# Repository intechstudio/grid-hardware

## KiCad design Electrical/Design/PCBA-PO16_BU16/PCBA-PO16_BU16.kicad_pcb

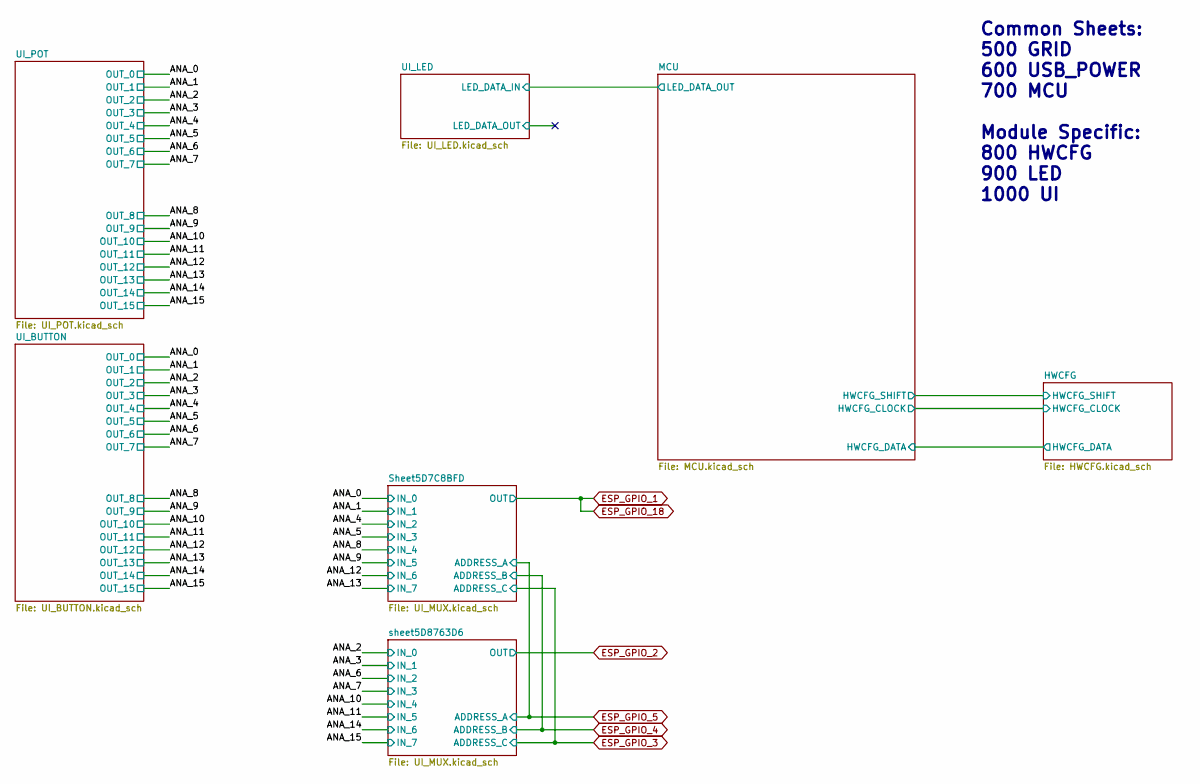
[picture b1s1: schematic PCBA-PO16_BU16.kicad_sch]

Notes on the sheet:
Common Sheets: 500 GRID 600 USB_POWER 700 MCU Module Specific: 800 HWCFG 900 LED 1000 UI

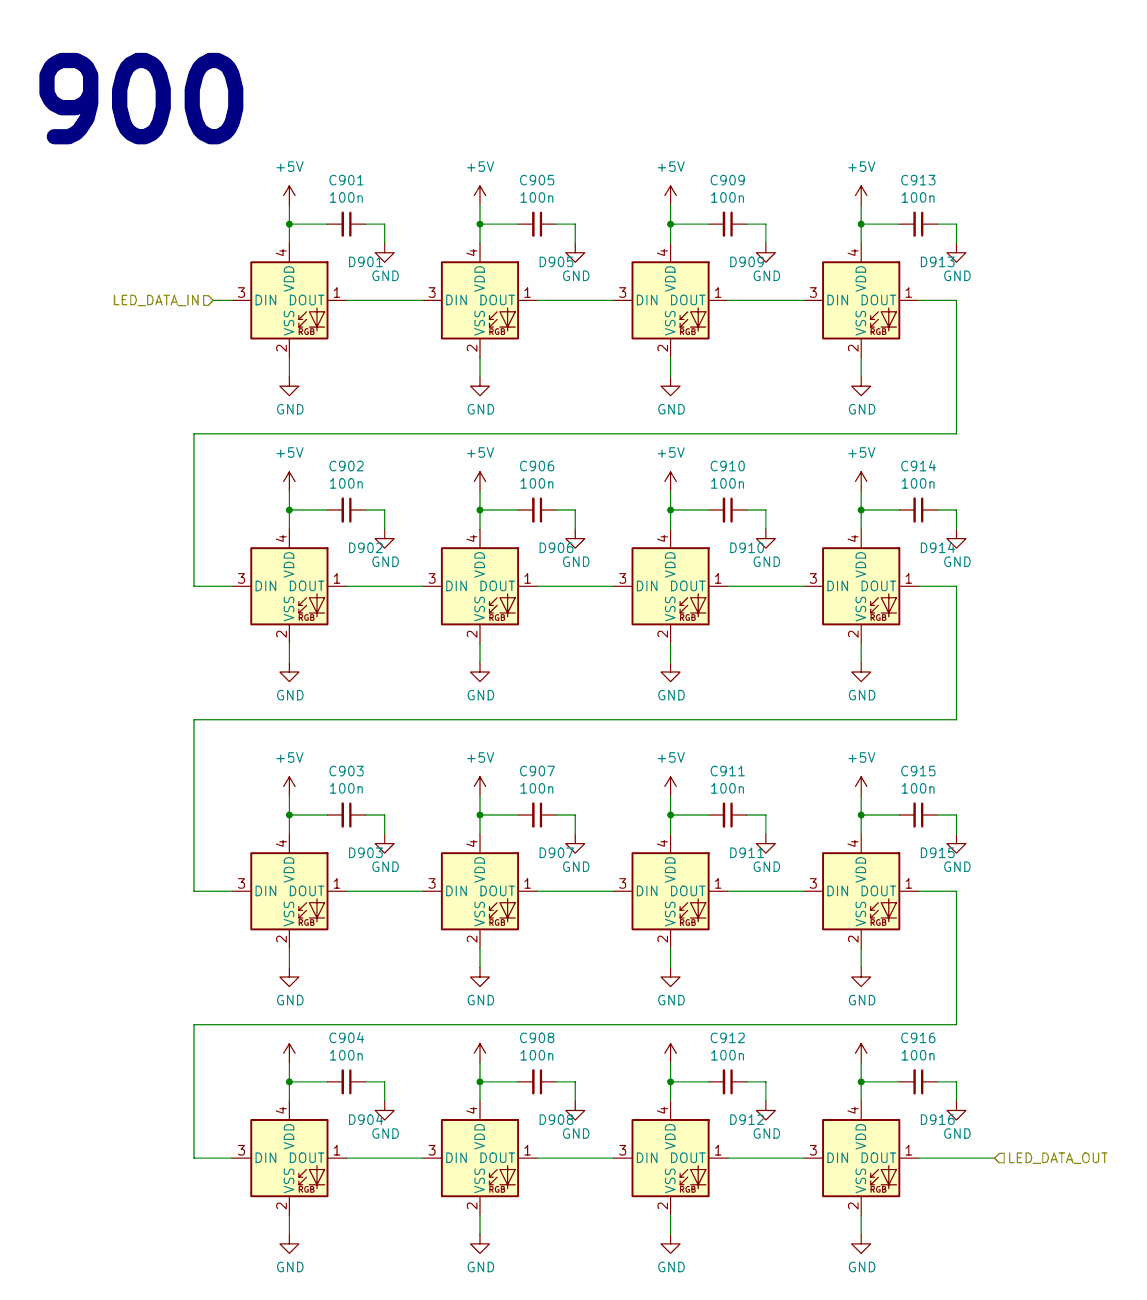
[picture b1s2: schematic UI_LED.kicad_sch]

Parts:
C901, C902, C903, C904, C905, C906, C907, C908, C909, C910, C911, C912, C913, C914, C915, C916: 100n; CAP_0402
D901, D902, D903, D904, D905, D906, D907, D908, D909, D910, D911, D912, D913, D914, D915, D916: WS2812C-2020; UI_WS2812C-2020

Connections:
+5V: C901.2, C902.2, C903.2, C904.2, C905.2, C906.2, C907.2, C908.2, C909.2, C910.2, C911.2, C912.2, C913.2, C914.2, C915.2, C916.2, D901.4 (VDD), D902.4 (VDD), D903.4 (VDD), D904.4 (VDD), D905.4 (VDD), D906.4 (VDD), D907.4 (VDD), D908.4 (VDD), D909.4 (VDD), D910.4 (VDD), D911.4 (VDD), D912.4 (VDD), D913.4 (VDD), D914.4 (VDD), D915.4 (VDD), D916.4 (VDD); also elsewhere on the board
/MCU/LED_DATA_OUT: D901.3 (DIN); also elsewhere on the board
/UI_LED/LED_DATA_OUT: D916.1 (DOUT)
unnamed: D901.1 (DOUT), D905.3 (DIN)
unnamed: D902.3 (DIN), D913.1 (DOUT)
unnamed: D902.1 (DOUT), D906.3 (DIN)
unnamed: D903.3 (DIN), D914.1 (DOUT)
unnamed: D903.1 (DOUT), D907.3 (DIN)
unnamed: D904.3 (DIN), D915.1 (DOUT)
unnamed: D904.1 (DOUT), D908.3 (DIN)
unnamed: D905.1 (DOUT), D909.3 (DIN)
unnamed: D906.1 (DOUT), D910.3 (DIN)
unnamed: D907.1 (DOUT), D911.3 (DIN)
unnamed: D908.1 (DOUT), D912.3 (DIN)
unnamed: D909.1 (DOUT), D913.3 (DIN)
unnamed: D910.1 (DOUT), D914.3 (DIN)
unnamed: D911.1 (DOUT), D915.3 (DIN)
unnamed: D912.1 (DOUT), D916.3 (DIN)

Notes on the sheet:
900

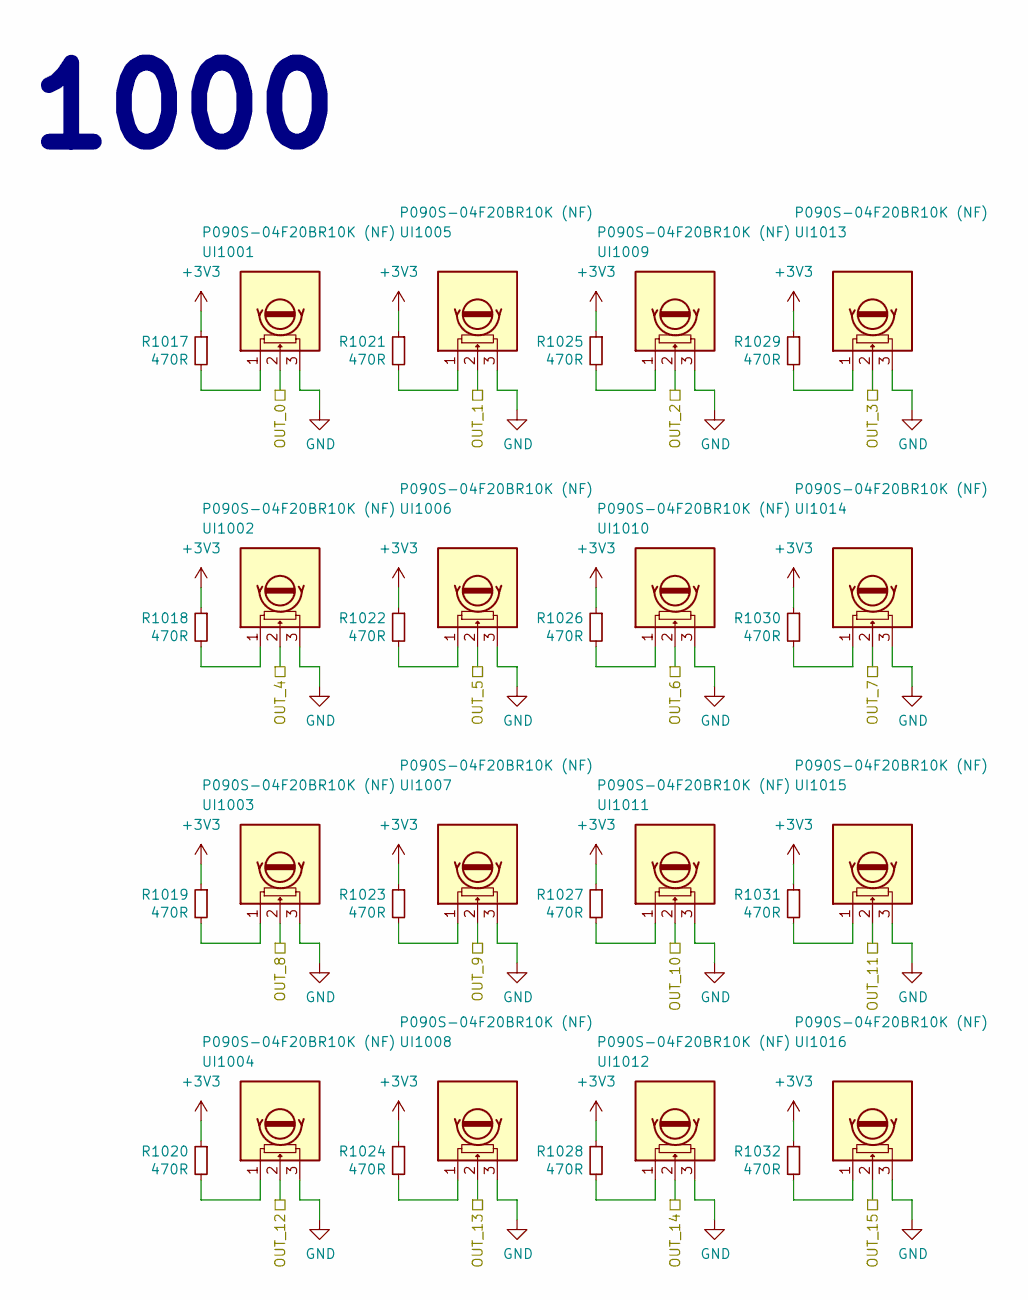
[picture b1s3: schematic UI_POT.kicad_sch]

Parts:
R1017, R1018, R1019, R1020, R1021, R1022, R1023, R1024, R1025, R1026, R1027, R1028, R1029, R1030, R1031, R1032: 470R; RES_0402
UI1001, UI1002, UI1003, UI1004, UI1005, UI1006, UI1007, UI1008, UI1009, UI1010, UI1011, UI1012, UI1013, UI1014, UI1015, UI1016: P090S-04F20BR10K (NF); UI_POT_TT

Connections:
/ANA_0: UI1001.2; also elsewhere on the board
/ANA_1: UI1005.2; also elsewhere on the board
/ANA_2: UI1009.2; also elsewhere on the board
/ANA_3: UI1013.2; also elsewhere on the board
/ANA_4: UI1002.2; also elsewhere on the board
/ANA_5: UI1006.2; also elsewhere on the board
/ANA_6: UI1010.2; also elsewhere on the board
/ANA_7: UI1014.2; also elsewhere on the board
/ANA_8: UI1003.2; also elsewhere on the board
/ANA_9: UI1007.2; also elsewhere on the board
/ANA_10: UI1011.2; also elsewhere on the board
/ANA_11: UI1015.2; also elsewhere on the board
/ANA_12: UI1004.2; also elsewhere on the board
/ANA_13: UI1008.2; also elsewhere on the board
/ANA_14: UI1012.2; also elsewhere on the board
/ANA_15: UI1016.2; also elsewhere on the board
unnamed: R1017.2, UI1001.1
unnamed: R1018.2, UI1002.1
unnamed: R1019.2, UI1003.1
unnamed: R1020.2, UI1004.1
unnamed: R1021.2, UI1005.1
unnamed: R1022.2, UI1006.1
unnamed: R1023.2, UI1007.1
unnamed: R1024.2, UI1008.1
unnamed: R1025.2, UI1009.1
unnamed: R1026.2, UI1010.1
unnamed: R1027.2, UI1011.1
unnamed: R1028.2, UI1012.1
unnamed: R1029.2, UI1013.1
unnamed: R1030.2, UI1014.1
unnamed: R1031.2, UI1015.1
unnamed: R1032.2, UI1016.1

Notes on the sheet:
1000

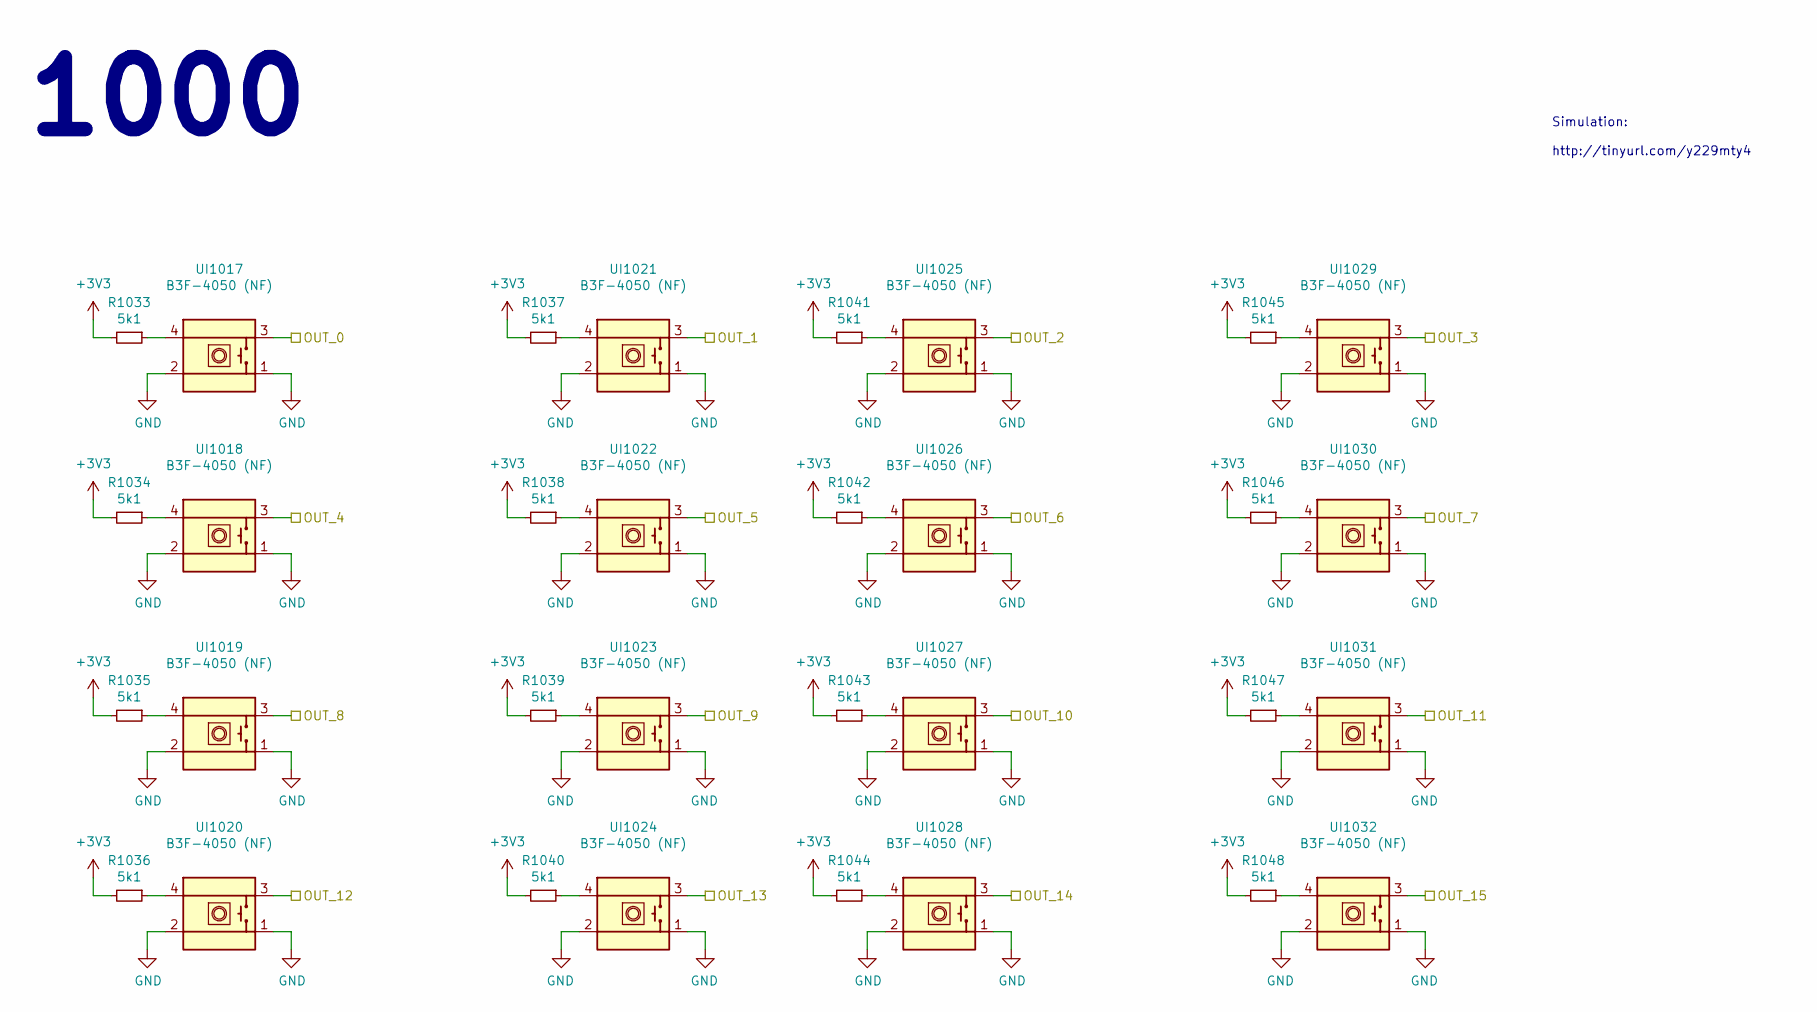
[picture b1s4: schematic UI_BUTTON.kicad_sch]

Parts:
R1033, R1034, R1035, R1036, R1037, R1038, R1039, R1040, R1041, R1042, R1043, R1044, R1045, R1046, R1047, R1048: 5k1; RES_0402
UI1017, UI1018, UI1019, UI1020, UI1021, UI1022, UI1023, UI1024, UI1025, UI1026, UI1027, UI1028, UI1029, UI1030, UI1031, UI1032: B3F-4050 (NF); UI_BUTTON_OMRON

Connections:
/ANA_0: UI1017.3; also elsewhere on the board
/ANA_1: UI1021.3; also elsewhere on the board
/ANA_2: UI1025.3; also elsewhere on the board
/ANA_3: UI1029.3; also elsewhere on the board
/ANA_4: UI1018.3; also elsewhere on the board
/ANA_5: UI1022.3; also elsewhere on the board
/ANA_6: UI1026.3; also elsewhere on the board
/ANA_7: UI1030.3; also elsewhere on the board
/ANA_8: UI1019.3; also elsewhere on the board
/ANA_9: UI1023.3; also elsewhere on the board
/ANA_10: UI1027.3; also elsewhere on the board
/ANA_11: UI1031.3; also elsewhere on the board
/ANA_12: UI1020.3; also elsewhere on the board
/ANA_13: UI1024.3; also elsewhere on the board
/ANA_14: UI1028.3; also elsewhere on the board
/ANA_15: UI1032.3; also elsewhere on the board
unnamed: R1033.1, UI1017.4
unnamed: R1034.1, UI1018.4
unnamed: R1035.1, UI1019.4
unnamed: R1036.1, UI1020.4
unnamed: R1037.1, UI1021.4
unnamed: R1038.1, UI1022.4
unnamed: R1039.1, UI1023.4
unnamed: R1040.1, UI1024.4
unnamed: R1041.1, UI1025.4
unnamed: R1042.1, UI1026.4
unnamed: R1043.1, UI1027.4
unnamed: R1044.1, UI1028.4
unnamed: R1045.1, UI1029.4
unnamed: R1046.1, UI1030.4
unnamed: R1047.1, UI1031.4
unnamed: R1048.1, UI1032.4

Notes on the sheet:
1000
Simulation: http://tinyurl.com/y229mty4

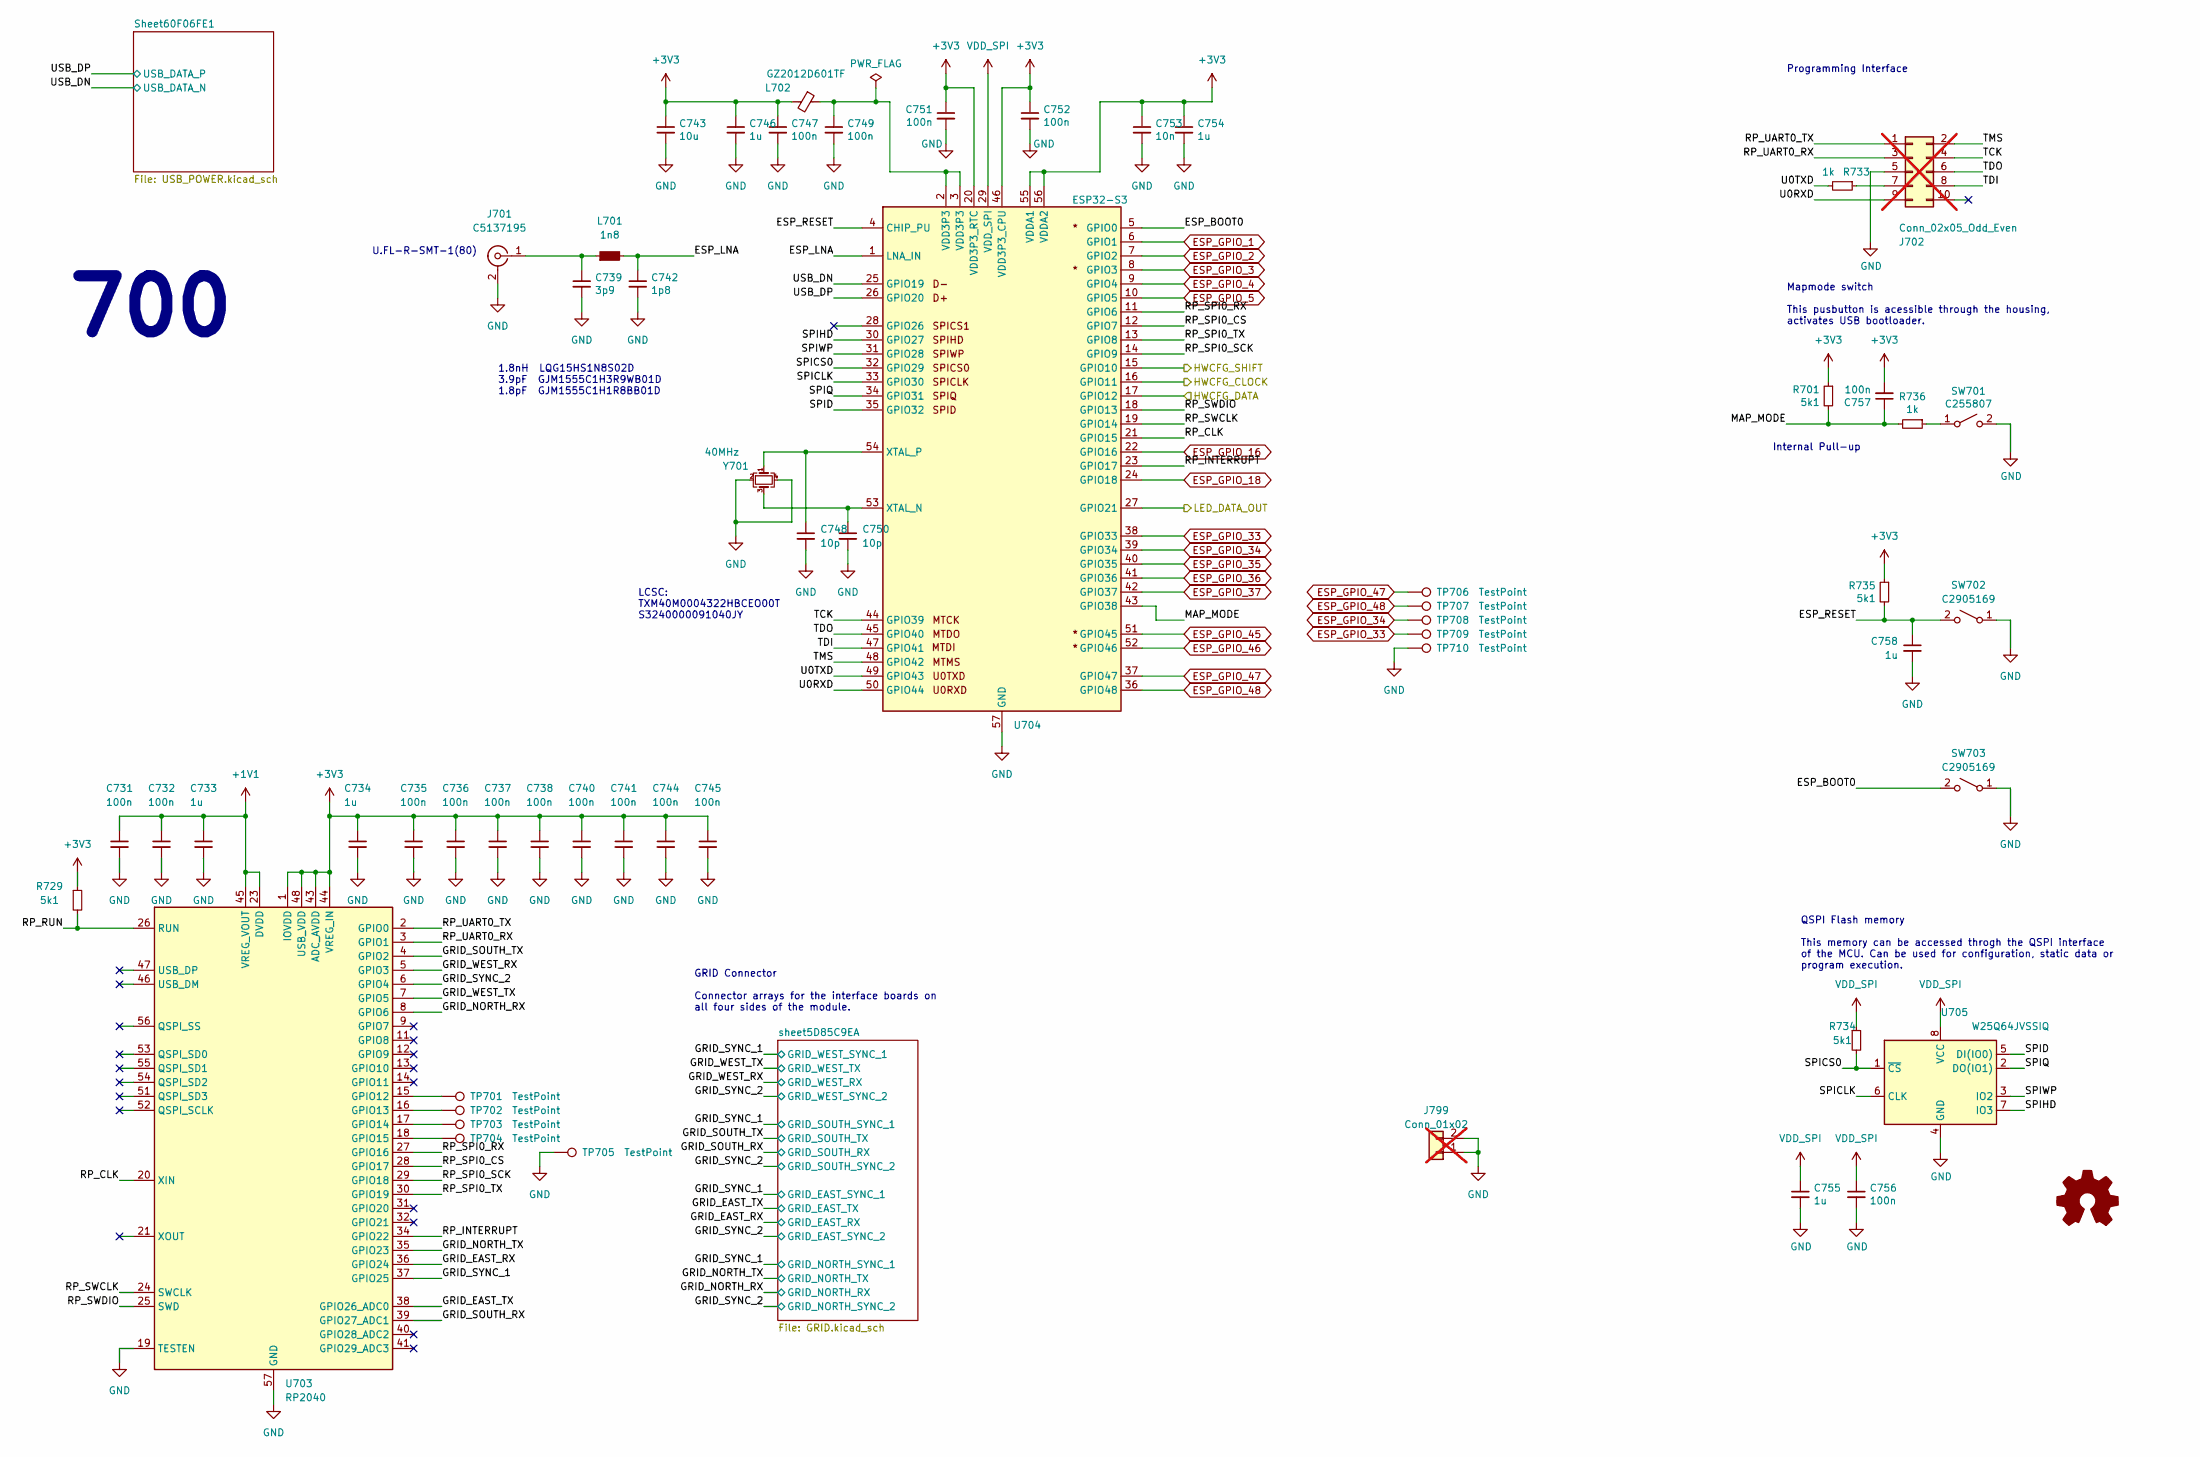
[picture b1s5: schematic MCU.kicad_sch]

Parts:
C731, C732, C735, C736, C737, C738, C740, C741, C744, C745, C747, C749, C751, C752, C756, C757: 100n; CAP_0402
C733, C734, C746, C754, C755, C758: 1u; CAP_0402
C739: 3p9; CAP_0402
C742: 1p8; CAP_0402
C743: 10u; CAP_0402
C748, C750: 10p; CAP_0402
C753: 10n; CAP_0402
J701: C5137195; U.FL_Molex_MCRF_73412-0110_Vertical
J702: Conn_02x05_Odd_Even; PinHeader_2x05_P1.27mm_Vertical; not fitted
J799: Conn_01x02; OscilloscopeGround; not fitted
L701: 1n8; IND_0402
L702: GZ2012D601TF; FERRIT_0805
LOGO701: OSHWA
R701, R729, R734, R735: 5k1; RES_0402
R733, R736: 1k; RES_0402
SW701: C255807; SW_HYP_MAPMODE
SW702, SW703: C2905169; SW_SPST_CK_RS282G05A3
TP701, TP702, TP703, TP704, TP706, TP707, TP708, TP709: TestPoint; TestPoint_Pad_D1.0mm
TP705, TP710: TestPoint; TestPoint_Pad_1.0x1.0mm
U703: RP2040; RP2040_QFN-56-1EP_7x7mm_P0.4mm_EP3.2x3.2mm
U704: ESP32-S3; QFN-56-1EP_7x7mm_P0.4mm_EP3.2x3.2mm
U705: W25Q64JVSSIQ; SOIC-8W_FLASH
Y701: 40MHz; Crystal_SMD_Abracon_ABM8G-4Pin_3.2x2.5mm

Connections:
+1V1: C731.1, C732.1, C733.1, U703.23 (DVDD), U703.45 (VREG_VOUT), U703.50 (DVDD)
/HWCFG/HWCFG_CLOCK: U704.16 (GPIO11); also elsewhere on the board
/HWCFG/HWCFG_DATA: U704.17 (GPIO12); also elsewhere on the board
/HWCFG/HWCFG_SHIFT: U704.15 (GPIO10); also elsewhere on the board
/MCU/ESP_BOOT0: SW703.2 (B), U704.5 (GPIO0)
/MCU/ESP_LNA: C742.1, L701.2, U704.1 (LNA_IN)
/MCU/ESP_RESET: C758.1, R735.2, SW702.2 (B), U704.4 (CHIP_PU)
/MCU/GRID_EAST_RX: U703.36 (GPIO24); also elsewhere on the board
/MCU/GRID_EAST_TX: U703.38 (GPIO26_ADC0); also elsewhere on the board
/MCU/GRID_NORTH_RX: U703.8 (GPIO6); also elsewhere on the board
/MCU/GRID_NORTH_TX: U703.35 (GPIO23); also elsewhere on the board
/MCU/GRID_SOUTH_RX: U703.39 (GPIO27_ADC1); also elsewhere on the board
/MCU/GRID_SOUTH_TX: U703.4 (GPIO2); also elsewhere on the board
/MCU/GRID_SYNC_1: U703.37 (GPIO25); also elsewhere on the board
/MCU/GRID_SYNC_2: U703.6 (GPIO4); also elsewhere on the board
/MCU/GRID_WEST_RX: U703.5 (GPIO3); also elsewhere on the board
/MCU/GRID_WEST_TX: U703.7 (GPIO5); also elsewhere on the board
/MCU/LED_DATA_OUT: U704.27 (GPIO21); also elsewhere on the board
/MCU/MAP_MODE: C757.1, R701.2, R736.2, U704.43 (GPIO38)
/MCU/RP_CLK: U703.20 (XIN), U704.21 (GPIO15)
/MCU/RP_INTERRUPT: U703.34 (GPIO22), U704.23 (GPIO17)
/MCU/RP_RUN: R729.2, U703.26 (RUN)
/MCU/RP_SPI0_CS: U703.28 (GPIO17), U704.12 (GPIO7)
/MCU/RP_SPI0_RX: U703.27 (GPIO16), U704.11 (GPIO6)
/MCU/RP_SPI0_SCK: U703.29 (GPIO18), U704.14 (GPIO9)
/MCU/RP_SPI0_TX: U703.30 (GPIO19), U704.13 (GPIO8)
/MCU/RP_SWCLK: U703.24 (SWCLK), U704.19 (GPIO14)
/MCU/RP_SWDIO: U703.25 (SWD), U704.18 (GPIO13)
/MCU/RP_UART0_RX: J702.3, U703.3 (GPIO1)
/MCU/RP_UART0_TX: J702.1, U703.2 (GPIO0)
/MCU/SPICLK: U704.33 (GPIO30), U705.6 (CLK)
/MCU/SPICS0: R734.2, U704.32 (GPIO29), U705.1 (~CS)
/MCU/SPID: U704.35 (GPIO32), U705.5 (DI(IO0))
/MCU/SPIHD: U704.30 (GPIO27), U705.7 (IO3)
/MCU/SPIQ: U704.34 (GPIO31), U705.2 (DO(IO1))
/MCU/SPIWP: U704.31 (GPIO28), U705.3 (IO2)
/MCU/TCK: J702.4, U704.44 (GPIO39)
/MCU/TDI: J702.8, U704.47 (GPIO41)
/MCU/TDO: J702.6, U704.45 (GPIO40)
/MCU/TMS: J702.2, U704.48 (GPIO42)
/MCU/U0RXD: J702.9, U704.50 (GPIO44)
/MCU/U0TXD: R733.2, U704.49 (GPIO43)
/MCU/USB_DN: U704.25 (GPIO19); also elsewhere on the board
/MCU/USB_DP: U704.26 (GPIO20); also elsewhere on the board
ESP_GPIO_2: U704.7 (GPIO2); also elsewhere on the board
ESP_GPIO_3: U704.8 (GPIO3); also elsewhere on the board
ESP_GPIO_4: U704.9 (GPIO4); also elsewhere on the board
ESP_GPIO_5: U704.10 (GPIO5); also elsewhere on the board
ESP_GPIO_16: U704.22 (GPIO16)
ESP_GPIO_33: TP709.1, U704.38 (GPIO33)
ESP_GPIO_34: TP708.1, U704.39 (GPIO34)
ESP_GPIO_35: U704.40 (GPIO35)
ESP_GPIO_36: U704.41 (GPIO36)
ESP_GPIO_37: U704.42 (GPIO37)
ESP_GPIO_45: U704.51 (GPIO45)
ESP_GPIO_46: U704.52 (GPIO46)
ESP_GPIO_47: TP706.1, U704.37 (GPIO47)
ESP_GPIO_48: TP707.1, U704.36 (GPIO48)
unnamed: C749.1, L702.1, U704.2 (VDD3P3), U704.3 (VDD3P3)
unnamed: C739.1, J701.1 (In), L701.1
unnamed: J702.7, R733.1
unnamed: R736.1, SW701.1 (A)
unnamed: TP701.1, U703.15 (GPIO12)
unnamed: TP702.1, U703.16 (GPIO13)
unnamed: TP703.1, U703.17 (GPIO14)
unnamed: TP704.1, U703.18 (GPIO15)
unnamed: C750.1, U704.53 (XTAL_N), Y701.3
unnamed: C748.1, U704.54 (XTAL_P), Y701.1
VDD_SPI: C755.1, C756.1, R734.1, U704.29 (VDD_SPI), U705.8 (VCC)

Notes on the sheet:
Mapmode switch This pusbutton is acessible through the housing, activates USB bootloader.
700
LCSC: TXM40M0004322HBCEO00T S3240000091040JY
1.8nH LQG15HS1N8S02D 3.9pF GJM1555C1H3R9WB01D 1.8pF GJM1555C1H1R8BB01D
QSPI Flash memory This memory can be accessed throgh the QSPI interface of the MCU. Can be used for configuration, static data or program execution.
Internal Pull-up
GRID Connector Connector arrays for the interface boards on all four sides of the module.
U.FL-R-SMT-1(80)
Programming Interface

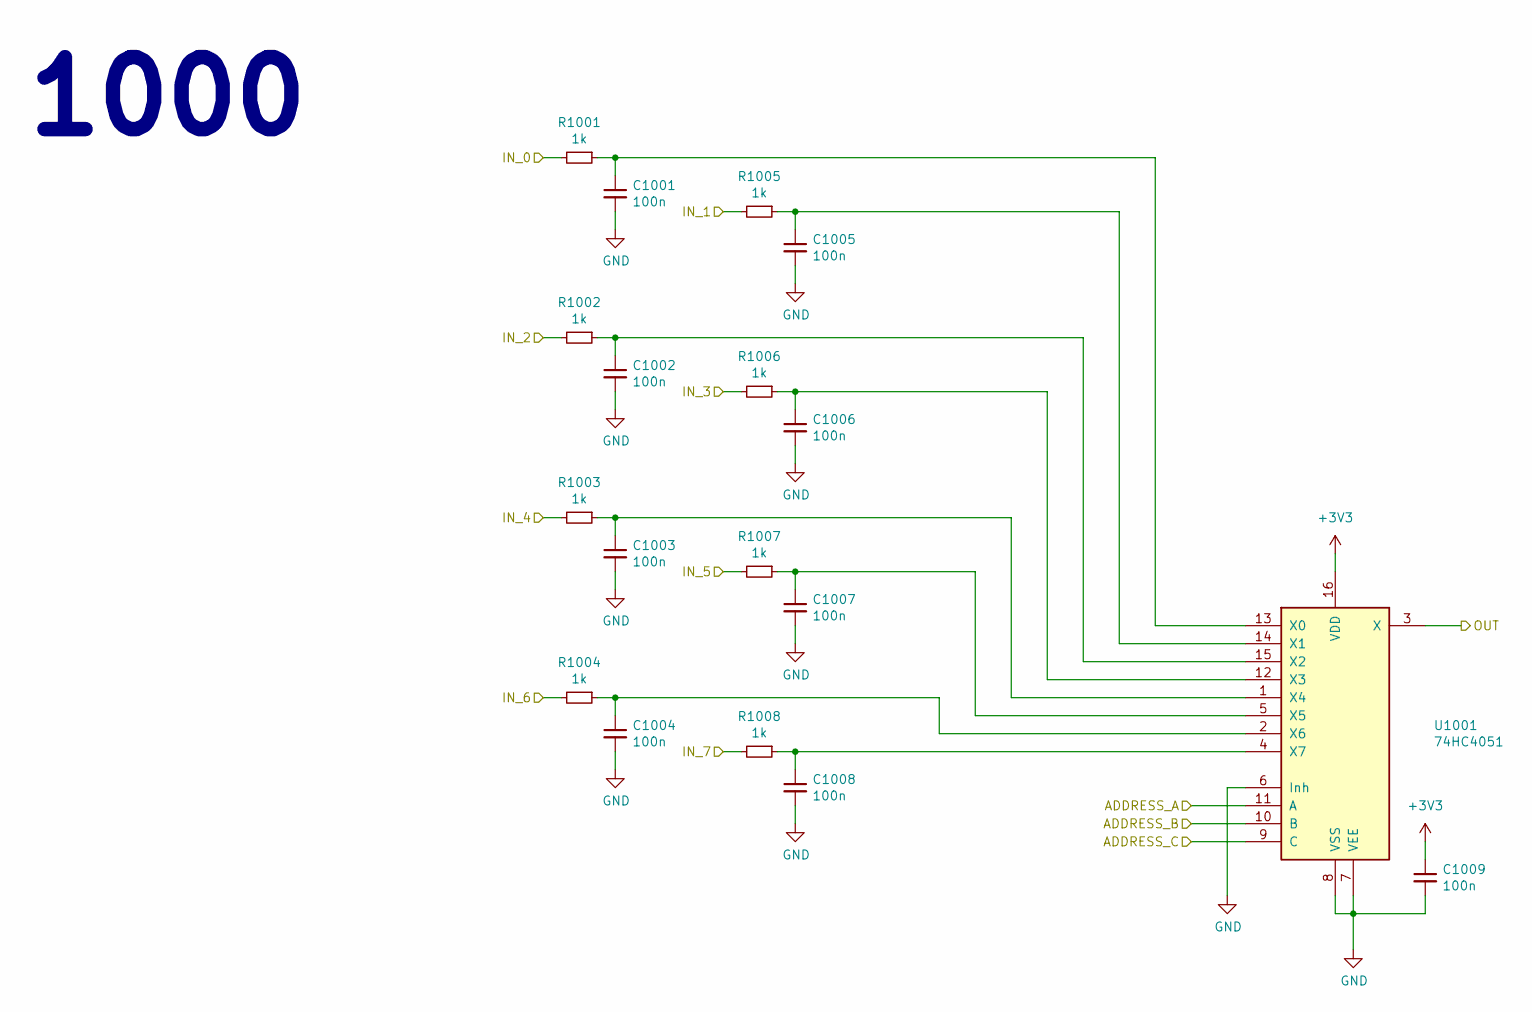
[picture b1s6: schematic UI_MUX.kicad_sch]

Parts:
C1001, C1002, C1003, C1004, C1005, C1006, C1007, C1008, C1009: 100n; CAP_0402
R1001, R1002, R1003, R1004, R1005, R1006, R1007, R1008: 1k; RES_0402
U1001: 74HC4051; SOIC-16_74HC4051

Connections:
/ANA_0: R1001.2; also elsewhere on the board
/ANA_1: R1005.2; also elsewhere on the board
/ANA_4: R1002.2; also elsewhere on the board
/ANA_5: R1006.2; also elsewhere on the board
/ANA_8: R1003.2; also elsewhere on the board
/ANA_9: R1007.2; also elsewhere on the board
/ANA_12: R1004.2; also elsewhere on the board
/ANA_13: R1008.2; also elsewhere on the board
ESP_GPIO_3: U1001.9 (C); also elsewhere on the board
ESP_GPIO_4: U1001.10 (B); also elsewhere on the board
ESP_GPIO_5: U1001.11 (A); also elsewhere on the board
unnamed: C1001.1, R1001.1, U1001.13 (X0)
unnamed: C1005.1, R1005.1, U1001.14 (X1)
unnamed: C1002.1, R1002.1, U1001.15 (X2)
unnamed: C1006.1, R1006.1, U1001.12 (X3)
unnamed: C1003.1, R1003.1, U1001.1 (X4)
unnamed: C1007.1, R1007.1, U1001.5 (X5)
unnamed: C1004.1, R1004.1, U1001.2 (X6)
unnamed: C1008.1, R1008.1, U1001.4 (X7)

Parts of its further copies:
C1010, C1011, C1012, C1013, C1014, C1015, C1016, C1017, C1018: 100n; CAP_0402
R1009, R1010, R1011, R1012, R1013, R1014, R1015, R1016: 1k; RES_0402
U1002: 74HC4051; SOIC-16_74HC4051

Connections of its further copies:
/ANA_2: R1009.2; also elsewhere on the board
/ANA_3: R1013.2; also elsewhere on the board
/ANA_6: R1010.2; also elsewhere on the board
/ANA_7: R1014.2; also elsewhere on the board
/ANA_10: R1011.2; also elsewhere on the board
/ANA_11: R1015.2; also elsewhere on the board
/ANA_14: R1012.2; also elsewhere on the board
/ANA_15: R1016.2; also elsewhere on the board
ESP_GPIO_2: U1002.3 (X); also elsewhere on the board
ESP_GPIO_3: U1002.9 (C); also elsewhere on the board
ESP_GPIO_4: U1002.10 (B); also elsewhere on the board
ESP_GPIO_5: U1002.11 (A); also elsewhere on the board
unnamed: C1010.1, R1009.1, U1002.13 (X0)
unnamed: C1014.1, R1013.1, U1002.14 (X1)
unnamed: C1011.1, R1010.1, U1002.15 (X2)
unnamed: C1015.1, R1014.1, U1002.12 (X3)
unnamed: C1012.1, R1011.1, U1002.1 (X4)
unnamed: C1016.1, R1015.1, U1002.5 (X5)
unnamed: C1013.1, R1012.1, U1002.2 (X6)
unnamed: C1017.1, R1016.1, U1002.4 (X7)

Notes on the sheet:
1000

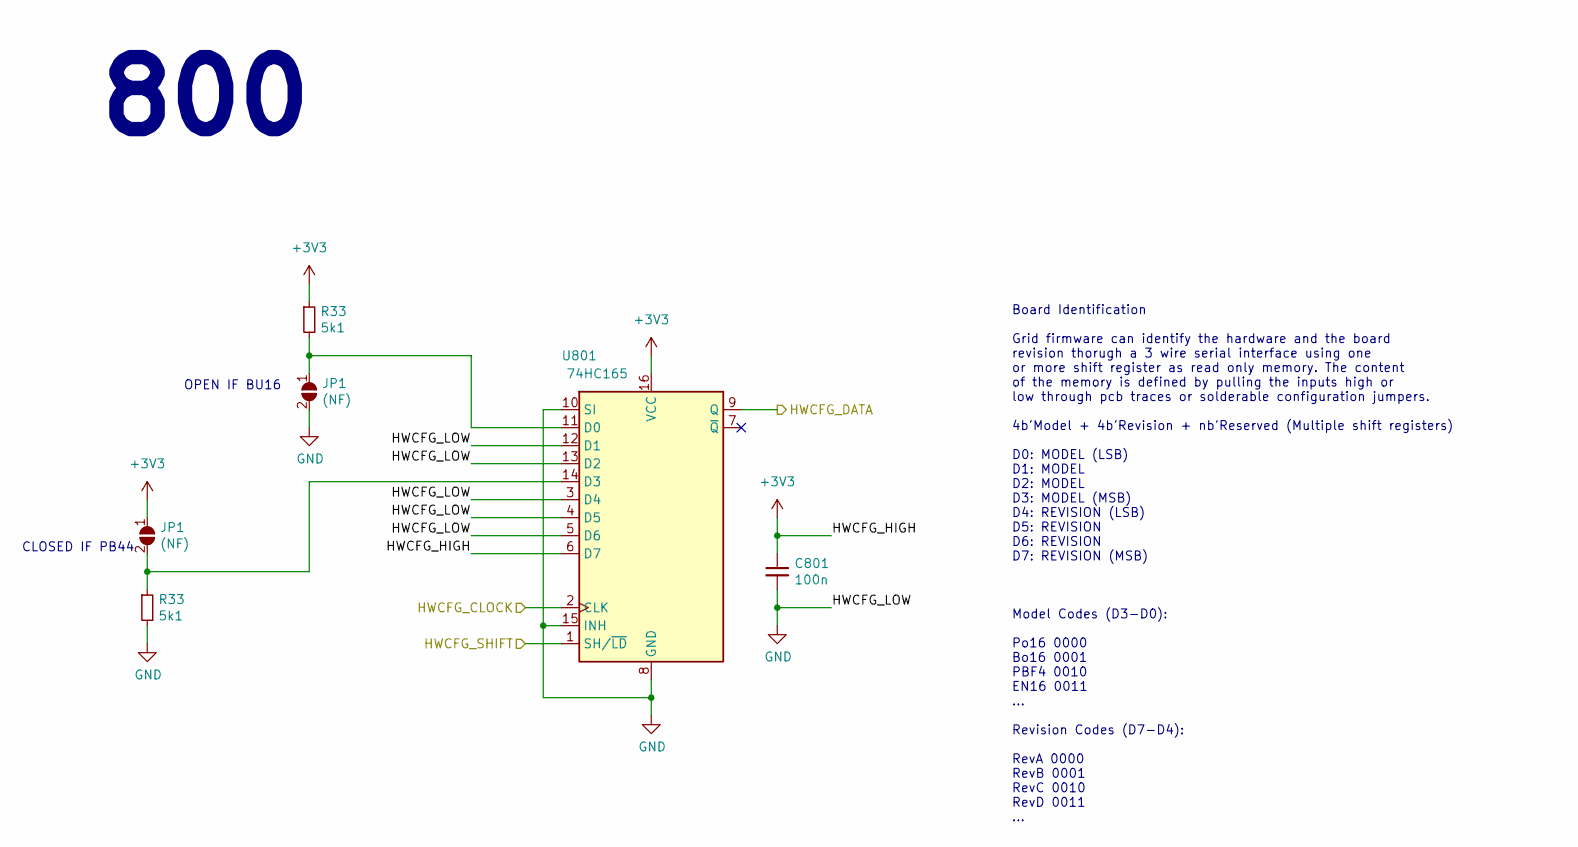
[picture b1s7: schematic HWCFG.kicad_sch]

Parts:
C801: 100n; CAP_0402
JP1: (NF); SolderJumper-2_P1.3mm_Open_TrianglePad1.0x1.5mm
R33: 5k1; RES_0402
U801: 74HC165; SOIC-16_74HC165

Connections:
/HWCFG/HWCFG_CLOCK: U801.2 (CLK); also elsewhere on the board
/HWCFG/HWCFG_DATA: U801.9 (Q); also elsewhere on the board
/HWCFG/HWCFG_SHIFT: U801.1 (SH/~LD); also elsewhere on the board
unnamed 98: U801.14 (D3); also elsewhere on the board
unnamed 99: U801.11 (D0); also elsewhere on the board

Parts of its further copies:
JP701, JP801: (NF); SolderJumper-2_P1.3mm_Open_TrianglePad1.0x1.5mm
R702, R801: 5k1; RES_0402

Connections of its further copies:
unnamed 98: JP701.2 (B), R702.1; also elsewhere on the board
unnamed 99: JP801.1 (A), R801.2; also elsewhere on the board

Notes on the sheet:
800
Board Identification Grid firmware can identify the hardware and the board revision thorugh a 3 wire serial interface using one or more shift register as read only memory. The content of the memory is defined by pulling the inputs high or low through pcb traces or solderable configuration jumpers. 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
CLOSED IF PB44
OPEN IF BU16

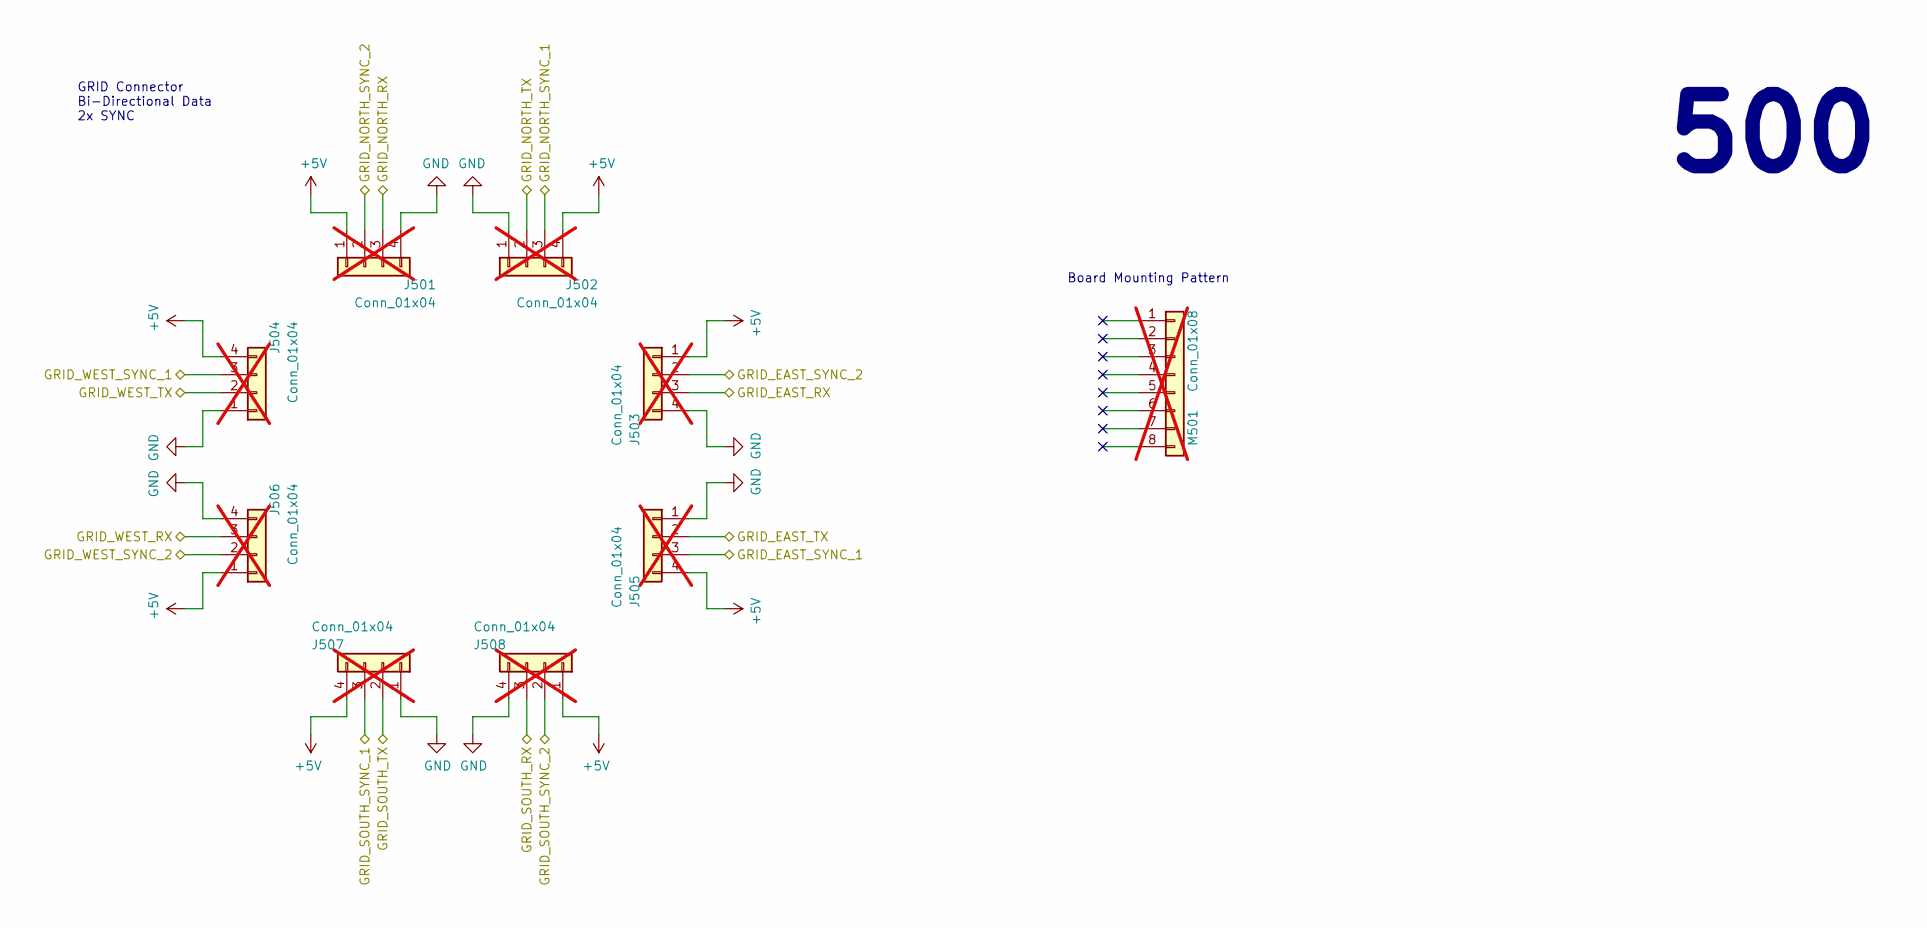
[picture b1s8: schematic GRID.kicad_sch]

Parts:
J501, J502, J503, J504, J505, J506, J507, J508: Conn_01x04; J_INTERFACE_SPRINGPATTERN; not fitted
M501: Conn_01x08; grid_outline; not fitted

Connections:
+5V: J501.1, J502.4, J503.1, J504.4, J505.4, J506.1, J507.4, J508.1; also elsewhere on the board
/MCU/GRID_EAST_RX: J503.3; also elsewhere on the board
/MCU/GRID_EAST_TX: J505.2; also elsewhere on the board
/MCU/GRID_NORTH_RX: J501.3; also elsewhere on the board
/MCU/GRID_NORTH_TX: J502.2; also elsewhere on the board
/MCU/GRID_SOUTH_RX: J508.3; also elsewhere on the board
/MCU/GRID_SOUTH_TX: J507.2; also elsewhere on the board
/MCU/GRID_SYNC_1: J502.3, J504.3, J505.3, J507.3; also elsewhere on the board
/MCU/GRID_SYNC_2: J501.2, J503.2, J506.2, J508.2; also elsewhere on the board
/MCU/GRID_WEST_RX: J506.3; also elsewhere on the board
/MCU/GRID_WEST_TX: J504.2; also elsewhere on the board

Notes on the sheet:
Board Mounting Pattern
GRID Connector Bi-Directional Data 2x SYNC
500

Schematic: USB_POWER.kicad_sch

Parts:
C601, C602: 1u; CAP_0402
C603: 4n7; CAP_0402
J601: TYPE-C-32-M-12; USB_C_Korean_Hroparts_TYPE-C-31-M-12
L601: GZ2012D601TF; FERRIT_0805
R601, R602: 5k1; RES_0402
R603: 1M; RES_0402
TP601: GND; TestPoint_Pad_1.0x1.0mm
TP602: VB; TestPoint_Pad_D1.0mm
TP603: D-; TestPoint_Pad_D1.0mm
TP604: D+; TestPoint_Pad_D1.0mm
TP605: UI; TestPoint_Pad_D1.0mm
U601: C5451661; SOT-23-6
U602: LN1134A332MR-G; SOT-23-5

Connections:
+5V: J601.A4B9 (VBUS), J601.A9B4 (VBUS), L601.2, TP602.1, U601.5; also elsewhere on the board
/MCU/USB_DN: J601.A7 (D-), J601.B7 (D-), TP603.1, U601.4, U601.6; also elsewhere on the board
/MCU/USB_DP: J601.A6 (D+), J601.B6 (D+), TP604.1, U601.1, U601.3; also elsewhere on the board
unnamed: C603.1, J601.S1 (SHIELD)
unnamed: J601.A5 (CC1), R601.1
unnamed: J601.B5 (CC2), R602.1
unnamed: J601.S2 (SHIELD), R603.1
unnamed: C601.1, L601.1, U602.1 (IN), U602.3 (EN)

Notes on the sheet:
ESD Diodes ESD protection for all of the externally accessible nets.
+3V3 LDO Regulators Regulators for generating independent power rails for the microcontroller and the user interface.
600

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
